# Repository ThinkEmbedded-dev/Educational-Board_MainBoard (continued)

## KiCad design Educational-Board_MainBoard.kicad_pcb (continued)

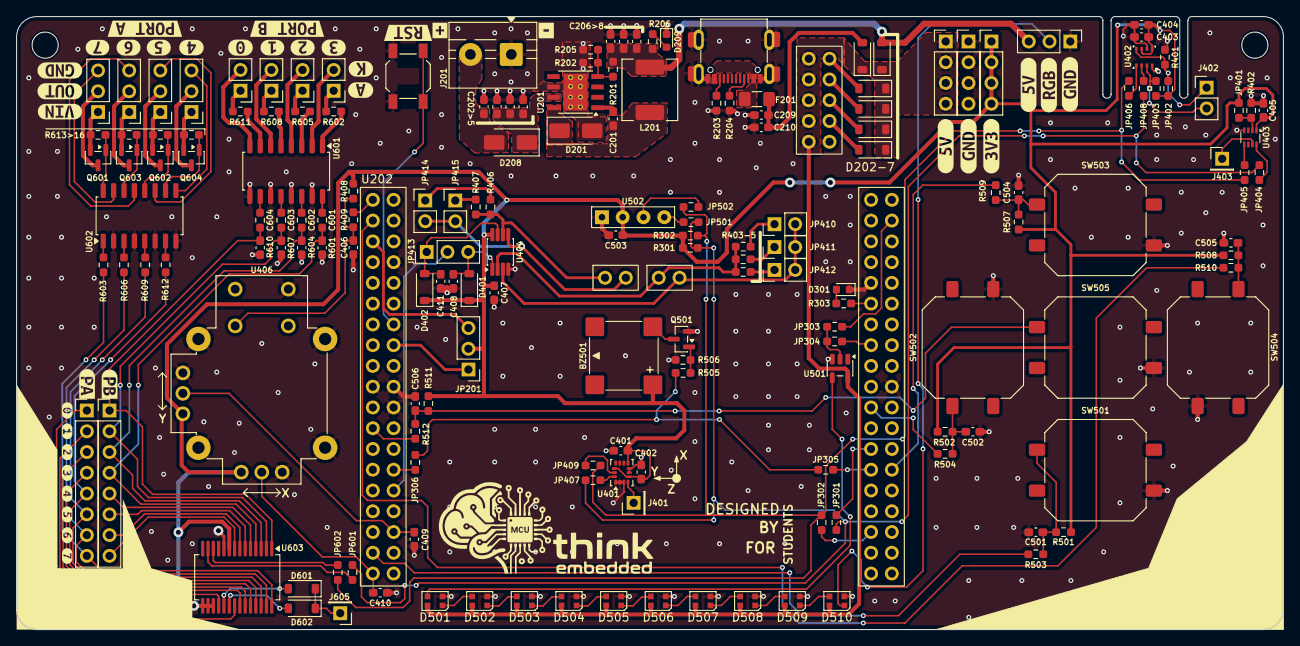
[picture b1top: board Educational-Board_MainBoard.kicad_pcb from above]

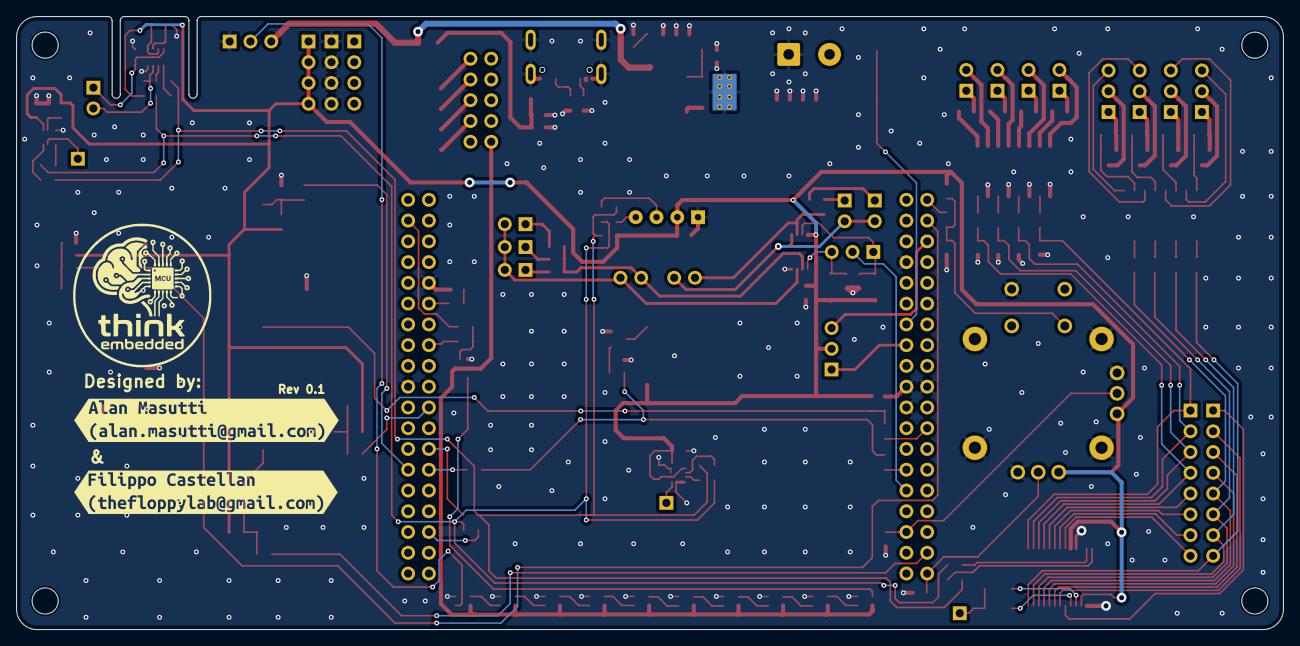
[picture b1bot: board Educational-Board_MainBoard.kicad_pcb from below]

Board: 2 copper layers, 155.0 x 75.0 mm, 218 parts (7 on the bottom side), 142 nets.

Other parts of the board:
kibuzzard-69F1C3A3: G***; kibuzzard-69F1C3A3
kibuzzard-69F1C3AE: G***; kibuzzard-69F1C3AE
kibuzzard-69F1C39D, kibuzzard-69F1C39D#2: G***; kibuzzard-69F1C39D
kibuzzard-69F1CCD6: G***; kibuzzard-69F1CCD6
kibuzzard-69F1CD88: G***; kibuzzard-69F1CD88
kibuzzard-69F3BF46: G***; kibuzzard-69F3BF46
kibuzzard-69F9D27B: G***; kibuzzard-69F9D27B
kibuzzard-69F9D252: G***; kibuzzard-69F9D252
kibuzzard-69F9F64C: G***; kibuzzard-69F9F64C
kibuzzard-69F9F66B: G***; kibuzzard-69F9F66B
kibuzzard-69F9F71E: G***; kibuzzard-69F9F71E
kibuzzard-69F9F605: G***; kibuzzard-69F9F605
kibuzzard-69F9F647: G***; kibuzzard-69F9F647
kibuzzard-69F9F651: G***; kibuzzard-69F9F651
kibuzzard-69F9F658: G***; kibuzzard-69F9F658
kibuzzard-69F9F712: G***; kibuzzard-69F9F712
kibuzzard-69F9F718: G***; kibuzzard-69F9F718
kibuzzard-69F9F723: G***; kibuzzard-69F9F723
kibuzzard-69F9F764: G***; kibuzzard-69F9F764
kibuzzard-69F2951E: G***; kibuzzard-69F2951E
kibuzzard-69FB5140: G***; kibuzzard-69FB5140
kibuzzard-69FCC61F: G***; kibuzzard-69FCC61F
kibuzzard-69FCC630: G***; kibuzzard-69FCC630
kibuzzard-69FCE76D: G***; kibuzzard-69FCE76D
kibuzzard-69FCE77B: G***; kibuzzard-69FCE77B
kibuzzard-69FCE77E: G***; kibuzzard-69FCE77E
kibuzzard-69FCE79E: G***; kibuzzard-69FCE79E
kibuzzard-69FCE761: G***; kibuzzard-69FCE761
kibuzzard-69FCE768: G***; kibuzzard-69FCE768
kibuzzard-69FCE770: G***; kibuzzard-69FCE770
kibuzzard-69FCE773: G***; kibuzzard-69FCE773
kibuzzard-69FCE777: G***; kibuzzard-69FCE777
kibuzzard-69FCE792: G***; kibuzzard-69FCE792
kibuzzard-69FCE911: G***; kibuzzard-69FCE911
kibuzzard-69FDFC10: G***; kibuzzard-69FDFC10

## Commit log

2025-09-29 Aggiunto nomi
2025-10-06 Aggiunti i file .lck al gitignore
2025-10-06 Aggiunto #auto_saved_files# a .gitignore
2026-01-11 Aggiunto schema generale alimentazione e UI. Da fare sourcing componenti
2026-02-28 Sistemato disaccoppiamento pulasnti, e aggiunto gyro i2c
2026-02-28 Created the connectors footpint library + started Nucleo64 footprint
2026-02-28 Added 3DModel + PowerSupply connector
2026-03-03 Added NUCLEO-H503RB symbol + created Nucleo64_ST_Morpho footprint
    - The footprint is created starting from Nucleo64 ones
    - The Nucleo Symbol is created and associated to the new footprint
2026-03-05 Added MCU sheet + added a button on the UI sheet
2026-03-06 Connected the nucleo to local nets
    - I created all the local lables to the MCU schematic and connected them to the corresponding pins of the Nucleo board.
    - I renumed the hierarchical sheets to be in order of importance
    - I added solder jumpers for making the board more versatile in some cases
    - Corrected the Nucleo pinout on the schematic symbol
2026-03-09 Added BME280 on Sensor sheet + Added Power frontend on the dedicated sheet + added I2C Resistors + minor changes
2026-03-09 Small changes
2026-03-09 Corrected nucleo symbol and footprint, Fixes #2
2026-03-09 Added Power connector of the nucleo to the schematic
2026-03-10 Added OPT4001, Fixes #4
2026-03-10 Added OPT4001 to schematic
2026-03-11 Added the hierarchical pins of the sheets and connected them, Fixes #7
2026-03-12 Added Joystick, Fixes #8
2026-03-12 Added hierarchical lablels to schematic
2026-03-12 fixed #1 , added protection circuit 5V selector jumper
2026-03-18 Changed the grounding of the opto-coupled power stage + Added UI connectors + Removed a Diode on the Power Sheet (Fixes #3)
2026-03-18 Completated the Power Schema + Added Shunts resistors with OP Amp + Connected the RGB Connector to the BUCK (Fixes #5)
2026-03-18 Runned ERC for the first time and fixed some errors
2026-03-18 Changed some value for grouping components
    Basically two resistors valued 5.1k and 5K1 have the same value
2026-03-21 Fixed some schematic issues
2026-03-25 Referenced the shematic and started the sourcing part
2026-03-25 added some lcsc code
2026-03-26 added some lcsc codes, changed reverse voltage protection with a diode
2026-03-28 added some lcsc PN, and uniformed some resistors values to reduce BOM count
2026-04-01 Created buzzer footprint, and fixed some libraries simbols and footprint
2026-04-01 Finished the sourcing of the components
2026-04-01 Started the checking of the components
2026-04-02 Continued to check components footprints
2026-04-22 Changed two connectors
2026-04-22 Started the floorplan + added the Power LED
2026-04-23 Continued the floor plan
2026-04-27 some placement
2026-04-27 Changed a bit the design, nothing important to note
2026-04-29 Fixed some errors on the SSD1306 footprint
2026-04-29 Added some netclasses + started routing of some small parts + reordered some groups
2026-04-29 Finished the netclass assignment
2026-04-29 Routed the buck stage
2026-04-29 Updated the SSD1316 footprint
2026-04-30 Roued the majority of the nets of the POWER IO
2026-04-30 Routed the another part of POWER_UI
2026-04-30 Continued routing + resized the board
2026-04-30 Some placing and routing
    Added joystick 3D model
2026-05-04 fixed i2c swap bridge (to be checked if now are ok) routed bme280
2026-05-05 Continuated routing + fixing SSD1306 footprint
2026-05-05 Routed most LEFT part of the board + modified button footprint + fixed some lables
2026-05-05 Resized the board at the left part
2026-05-06 Added some exclusion from DRC + changed the min height for silkscreen
2026-05-06 Continued the routing
2026-05-06 Finished the routing: TODO fixing IMU
2026-05-07 routing and silkscreen logo
2026-05-08 Added pullup to the joystick, Fixes #16
2026-05-12 Added placeholders connectors for the Nucleo - TO ADD LCSC CODES
2026-05-12 added version marking, generated all the production files, added last connector lcsc number
2026-05-13 Changed the Revision Number on the whole project
2026-05-13 added missing 3d models
2026-05-15 Changed the sheets of the project
2026-05-15 Added 3D models to the USB and on the LEDs
2026-05-16 Saved the project
2026-06-29 Changed the Nucleo Symbol to add Arduino Names + Rotated a I2C jumper near the LCD
